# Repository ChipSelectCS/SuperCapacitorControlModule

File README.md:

# SuperCapacitorControlModule
250W backup supercapacitor module that fully overtakes main supply line(22-26V) in case of exceeding a programed threshold power with ability for recharge

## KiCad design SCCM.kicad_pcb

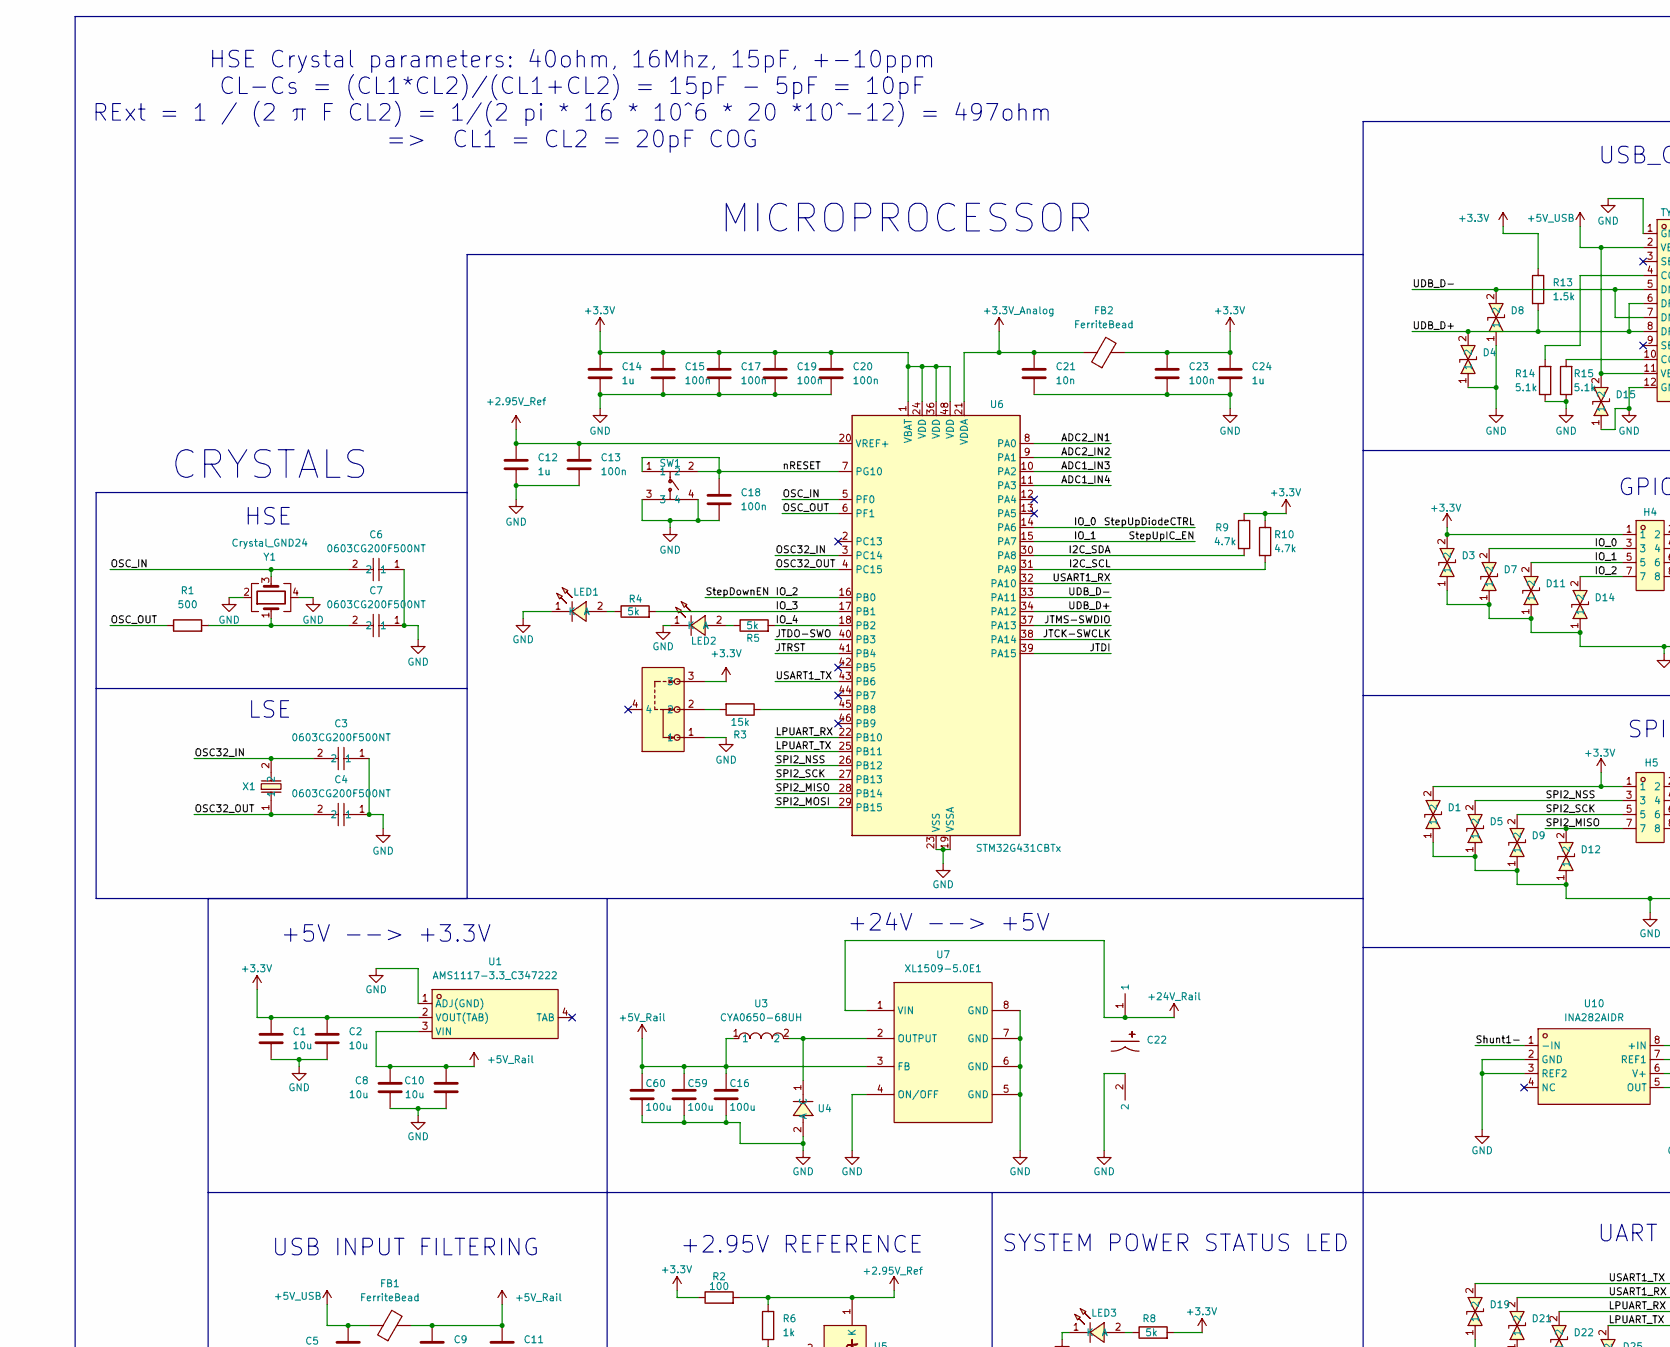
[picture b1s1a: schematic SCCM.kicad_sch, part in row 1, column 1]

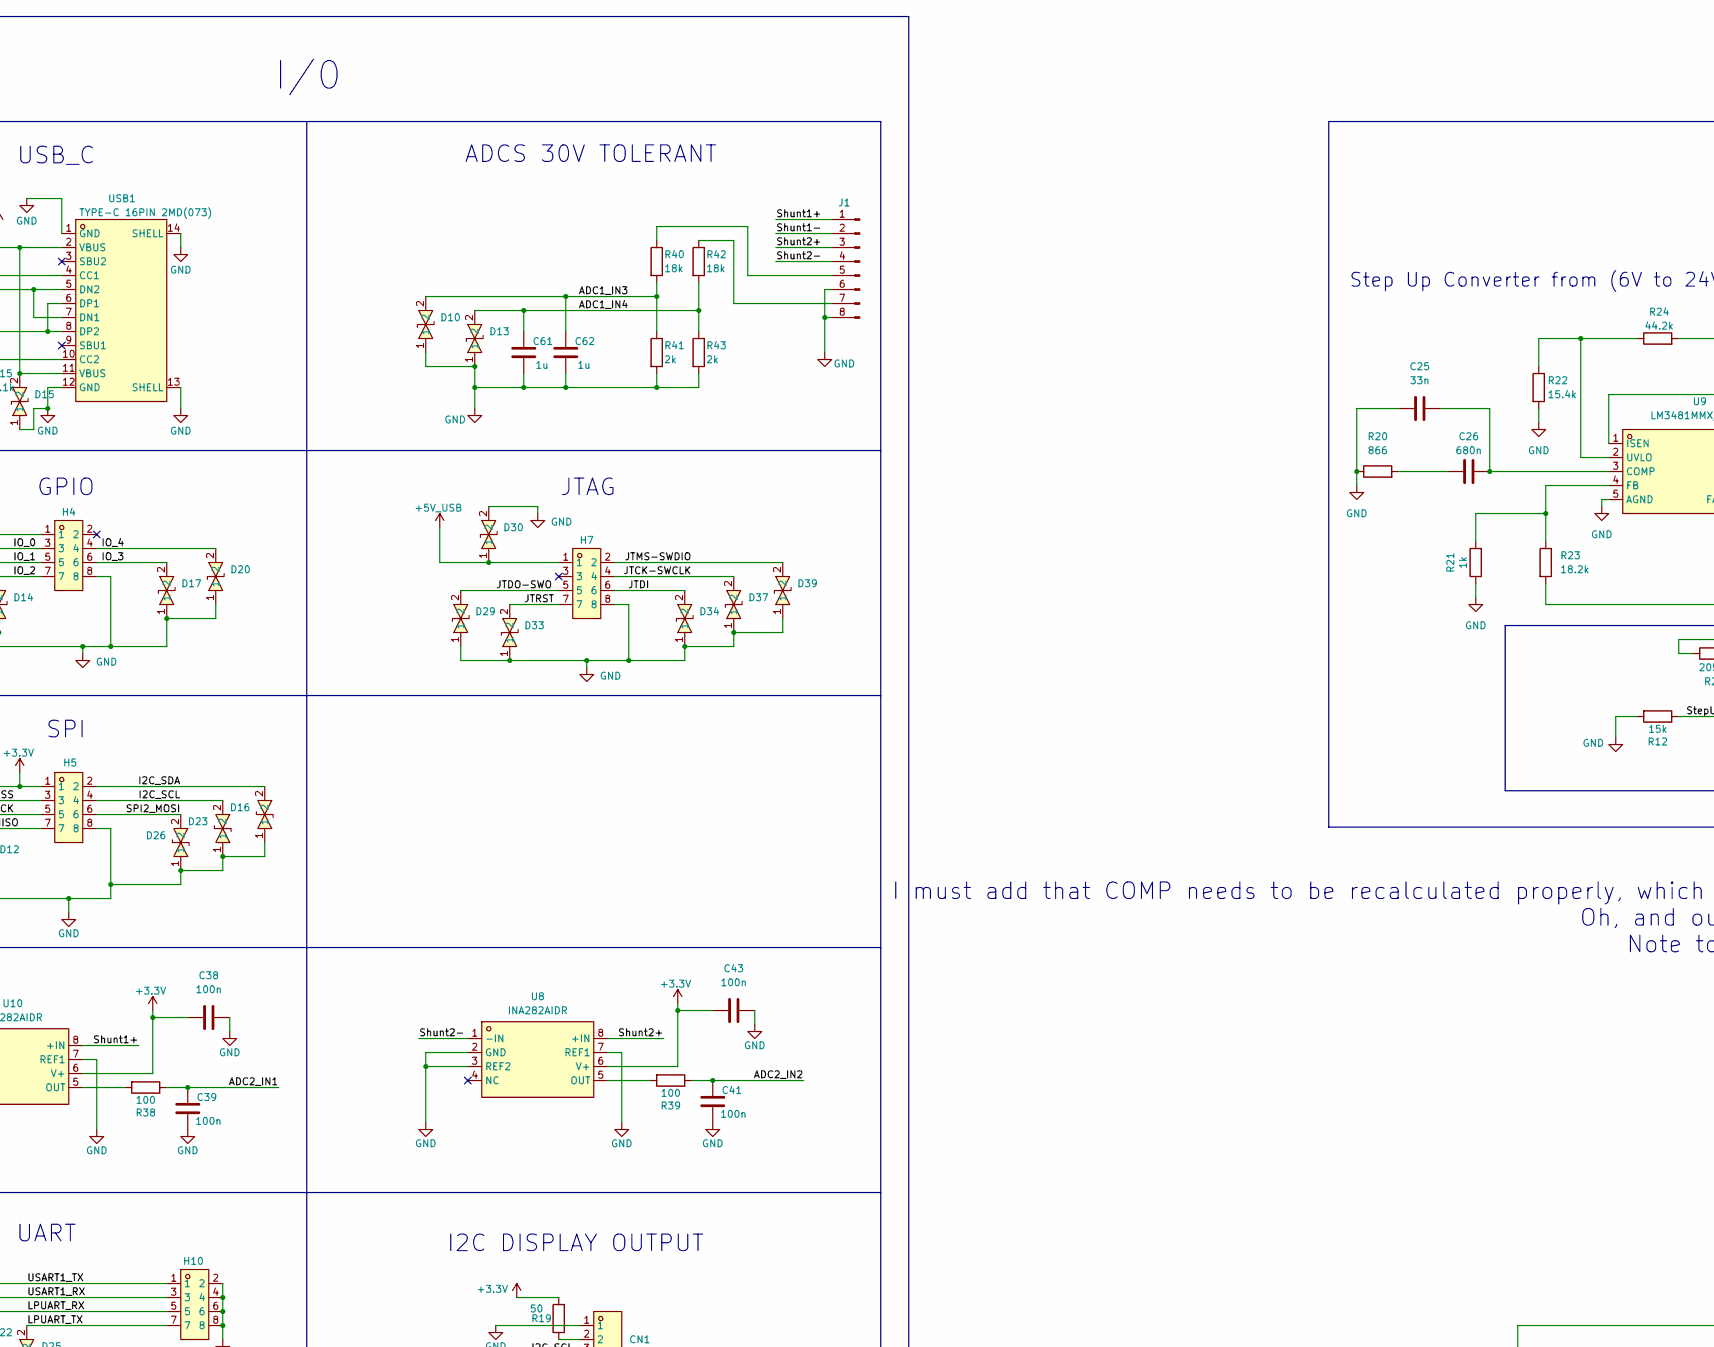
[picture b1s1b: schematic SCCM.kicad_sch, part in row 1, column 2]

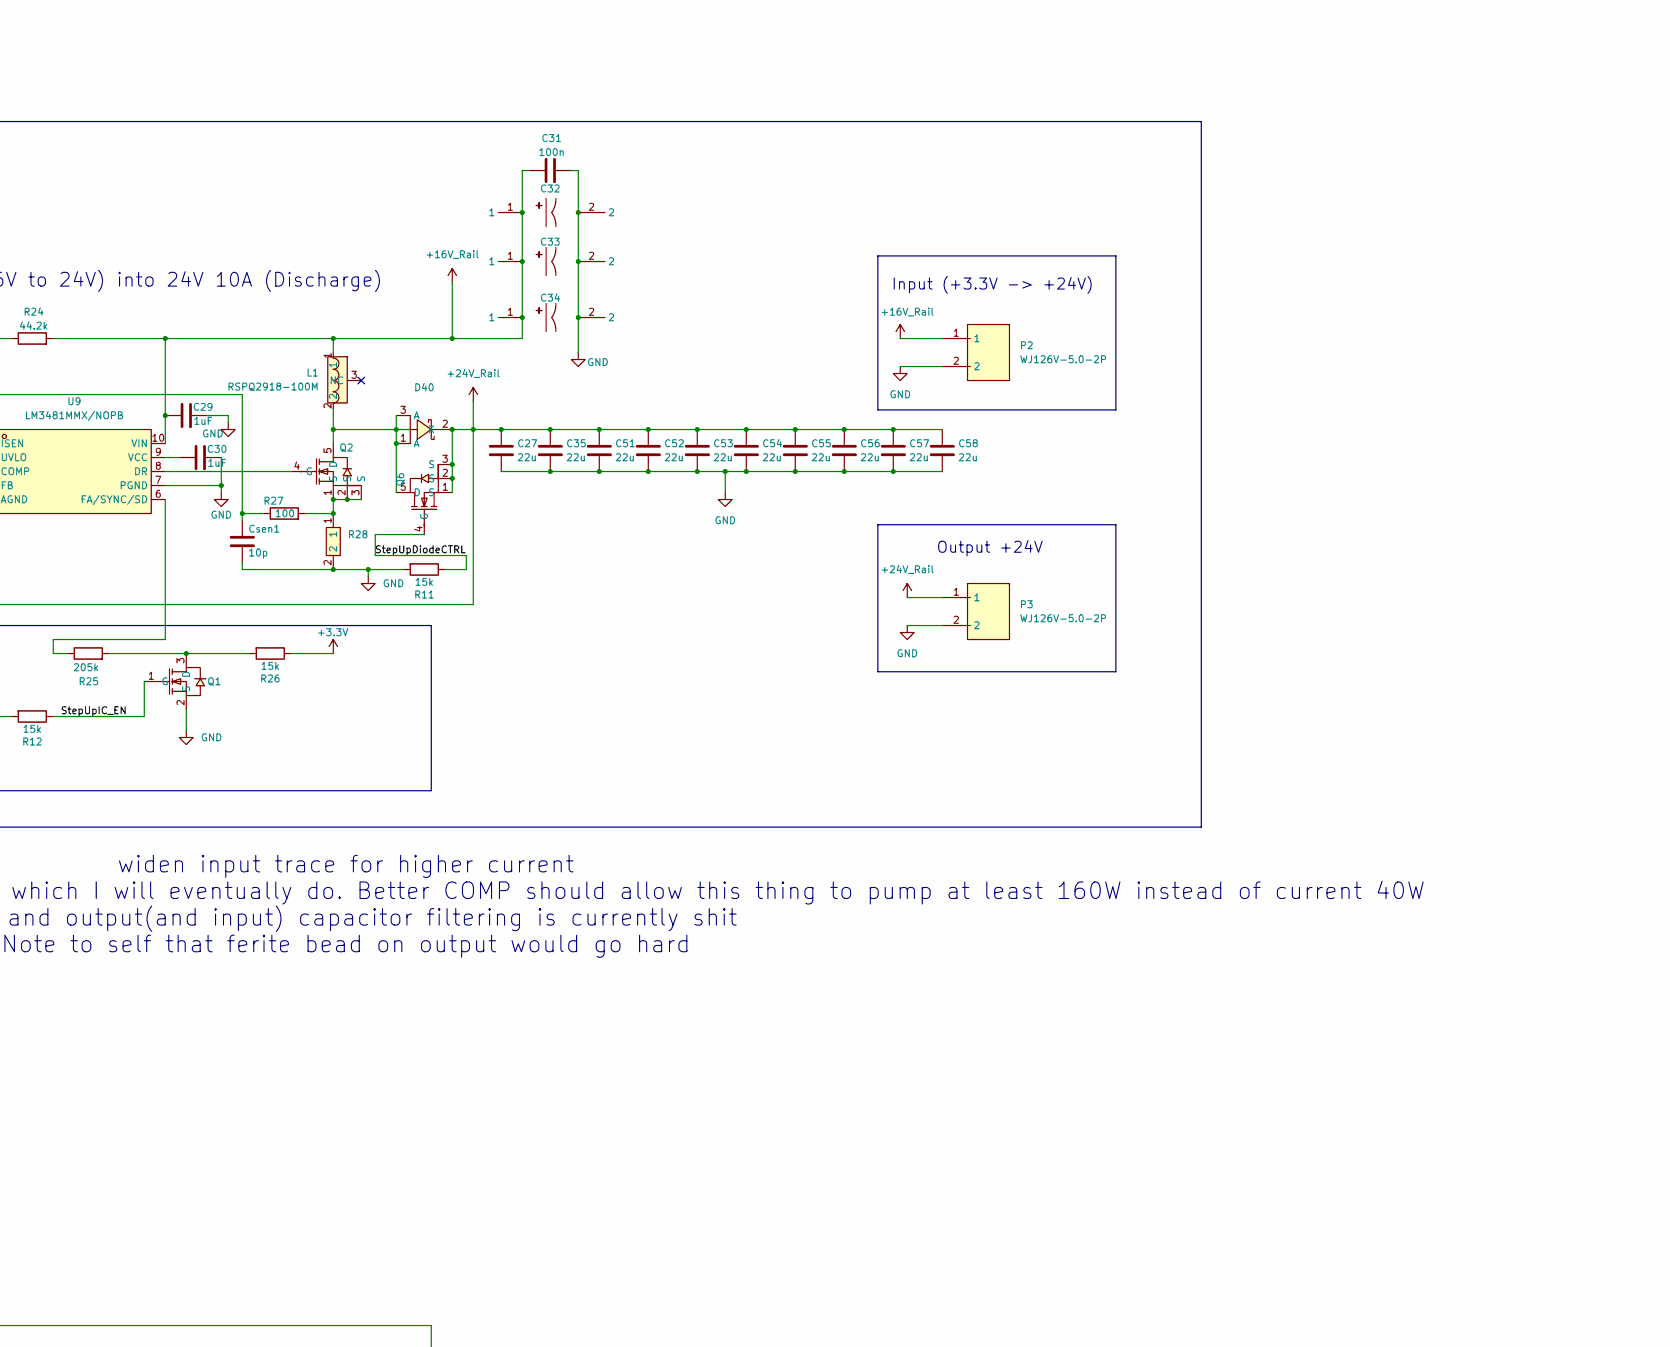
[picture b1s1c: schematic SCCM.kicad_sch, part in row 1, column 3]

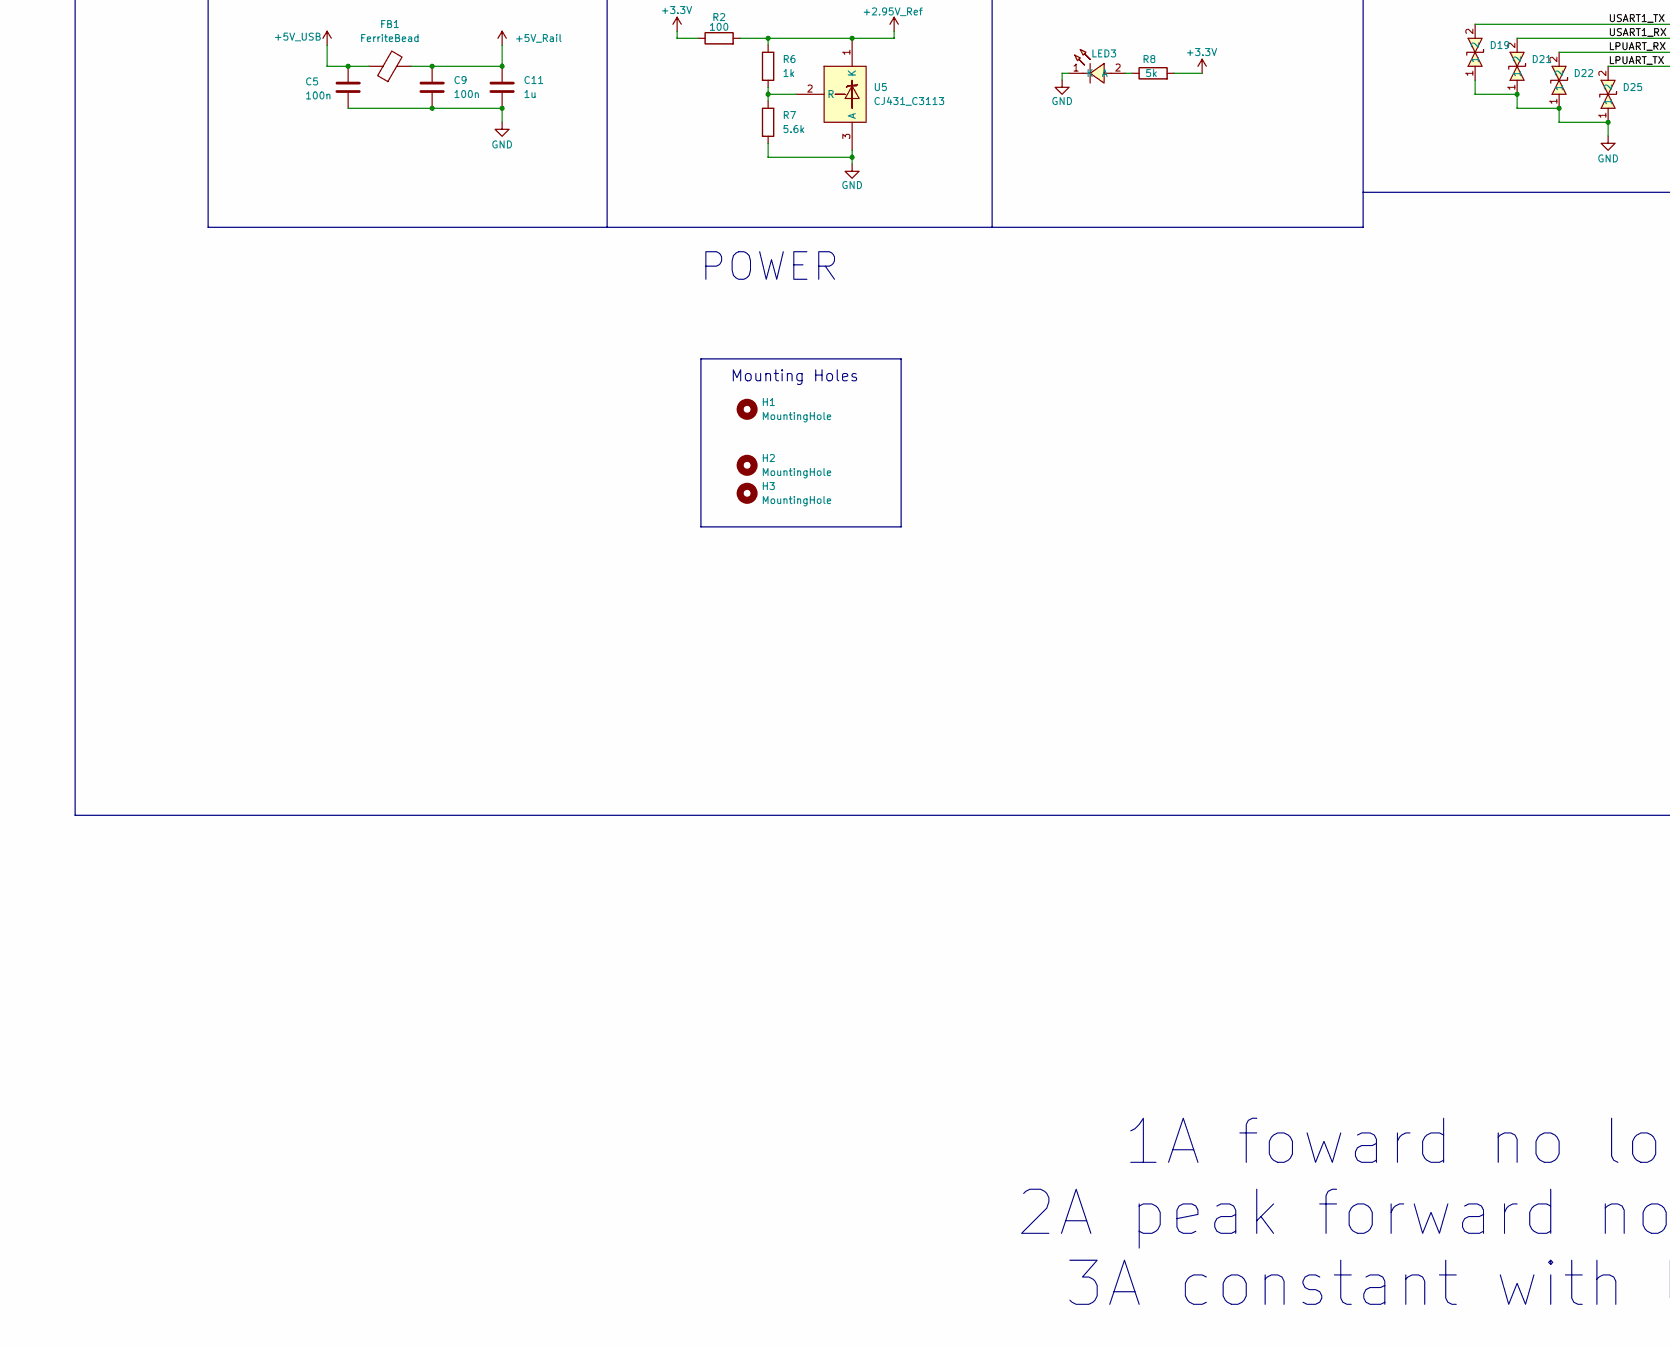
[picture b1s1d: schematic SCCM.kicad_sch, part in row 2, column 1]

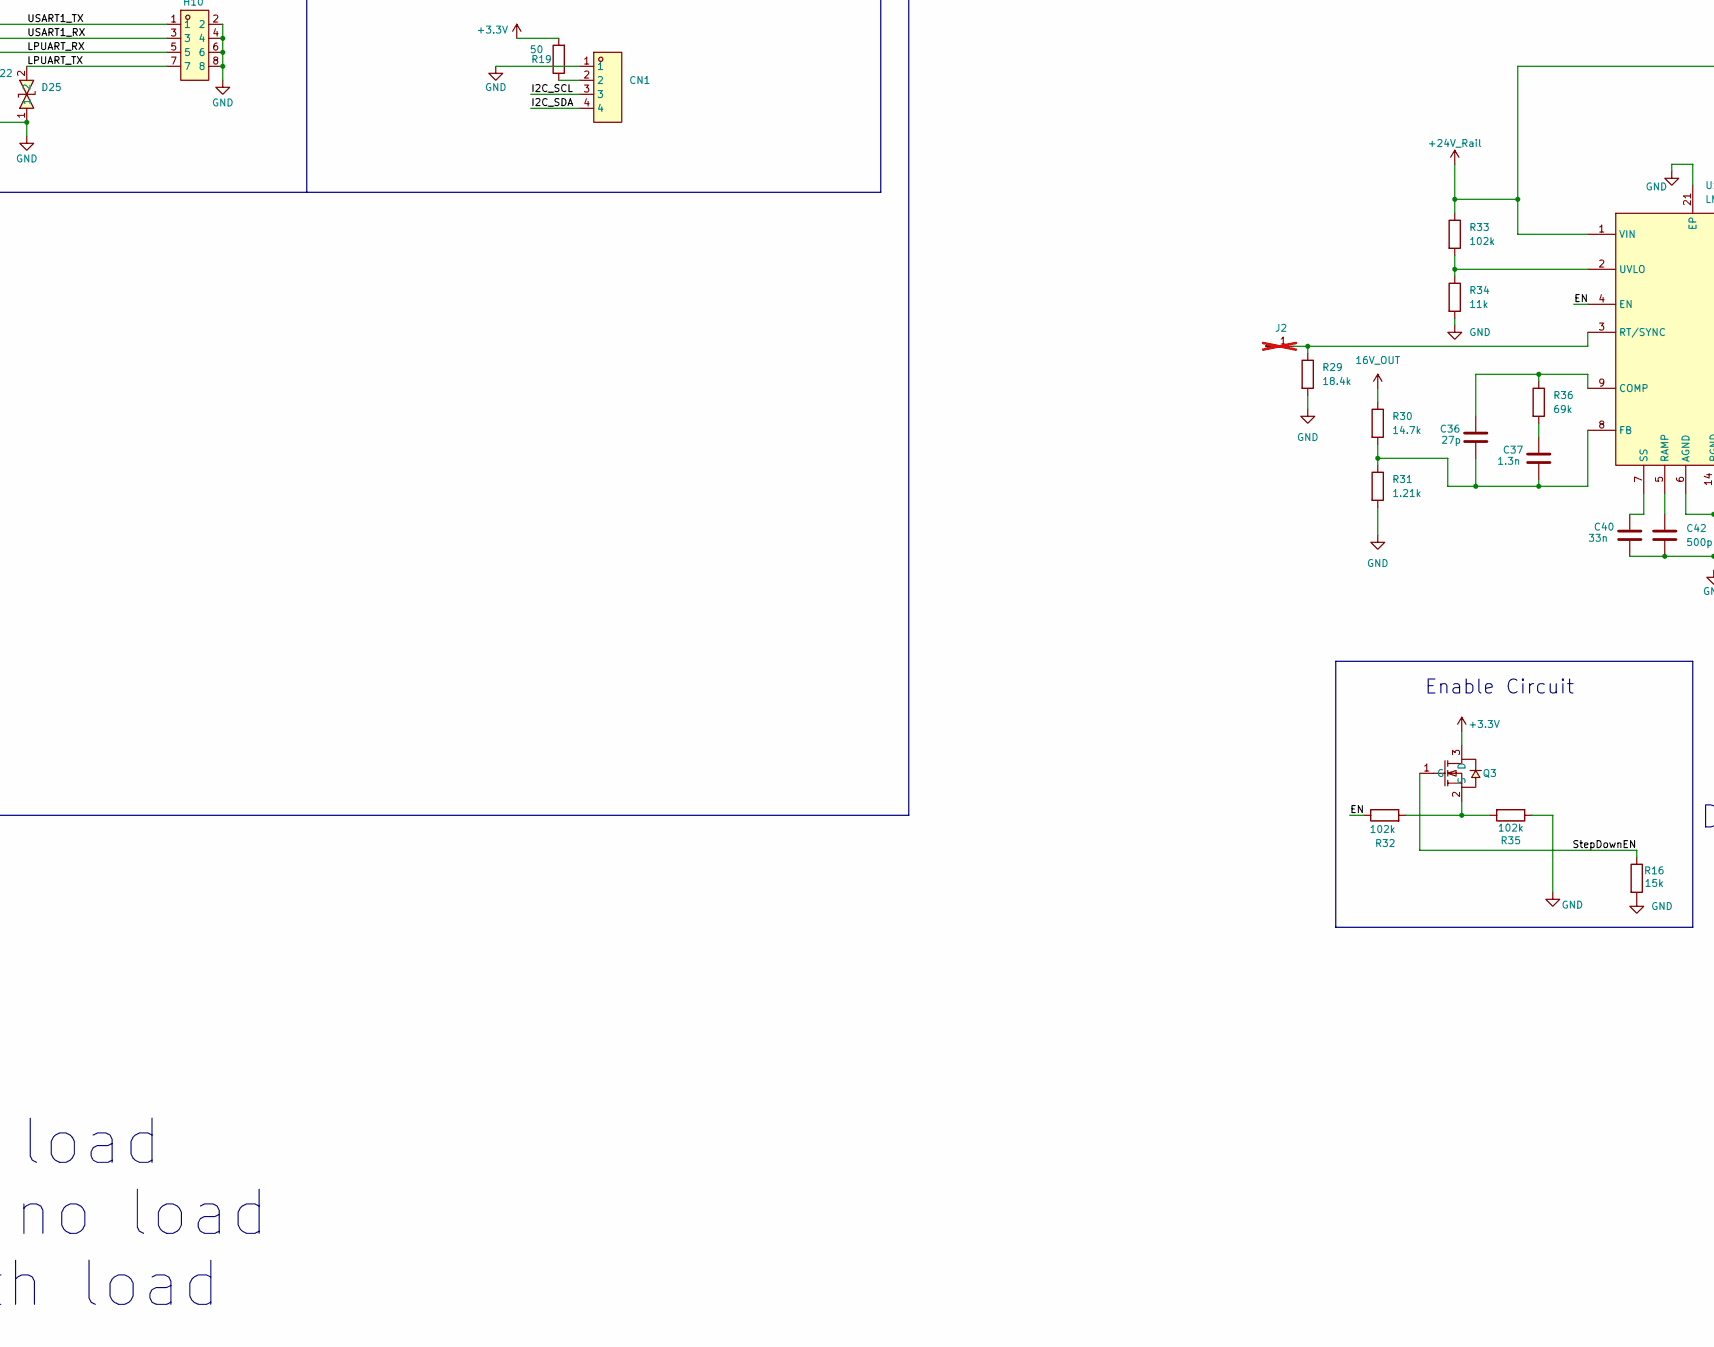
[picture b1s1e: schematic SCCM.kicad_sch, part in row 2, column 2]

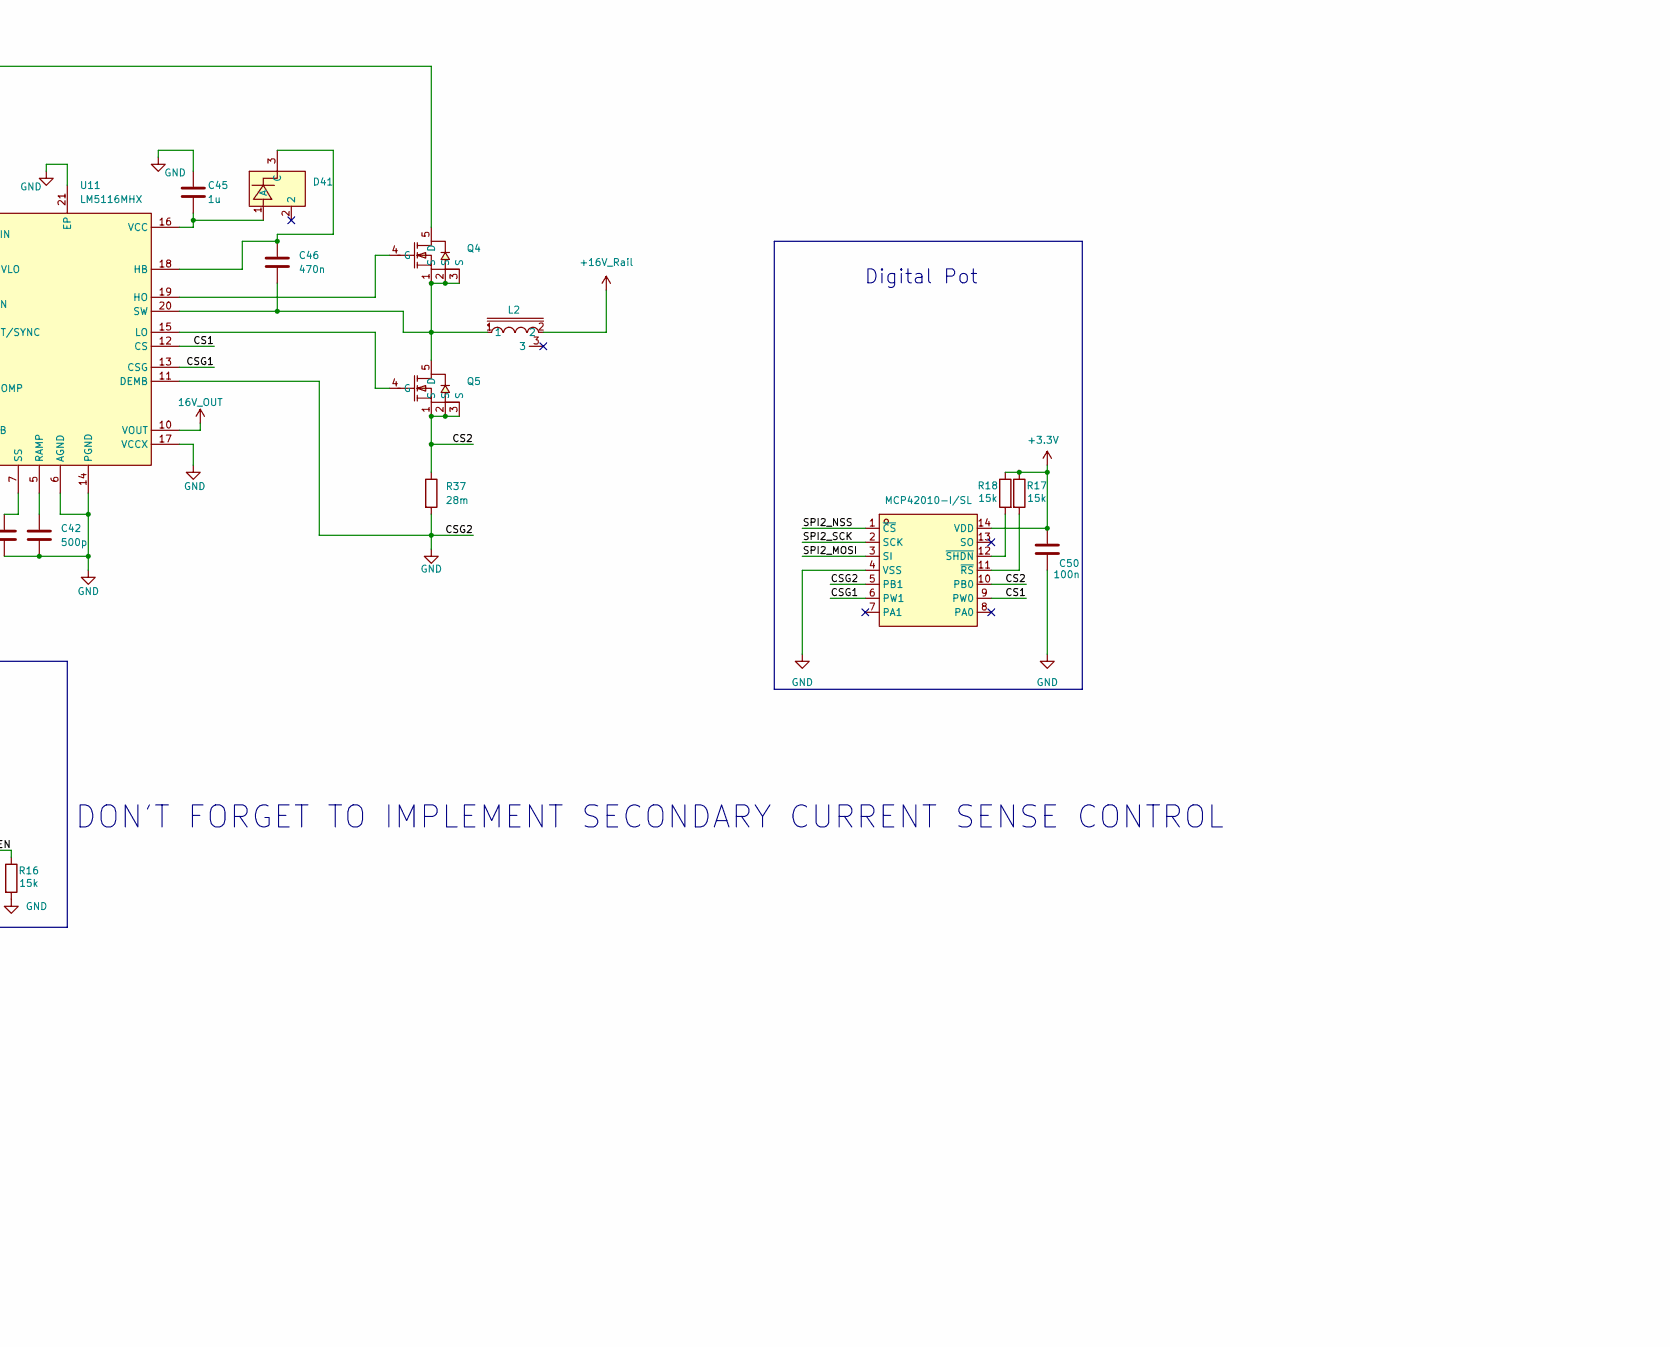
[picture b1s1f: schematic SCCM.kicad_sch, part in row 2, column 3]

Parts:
C1, C2, C8, C10: 10u; C_0603_1608Metric
C3, C4, C6, C7: 0603CG200F500NT; C0603; LCSC Part C165732
C5, C9, C13, C15, C17, C18, C19, C20, C23, C31, C38, C39, C41, C43, C50: 100n; C_0603_1608Metric
C11, C12, C14, C24, C45, C61, C62: 1u; C_0603_1608Metric
C16, C59, C60: 100u; C_1206_3216Metric; LCSC Part C7432784
C21: 10n; C_0603_1608Metric
C22, C32, C33, C34: HV1H227M1010PZ; CAP-SMD_BD10.0-L10.3-W10.3-LS11.3-FD; LCSC Part C5246564
C25, C40: 33n; C_0603_1608Metric
C26: 680n; C_0603_1608Metric
C27, C35, C51, C52, C53, C54, C55, C56, C57, C58: 22u; C_0805_2012Metric; LCSC Part C6119901
C29, C30: 1uF; C_0603_1608Metric
C36: 27p; C_0603_1608Metric
C37: 1.3n; C_0603_1608Metric
C42: 500p; C_0603_1608Metric
C46: 470n; C_0603_1608Metric
CN1: F136-1104S3CMUB2; HDR-SMD_4P-P2.54-V-M-LS5.0; LCSC Part C20071191
Csen1: 10p; C_0603_1608Metric
D1, D3, D4, D5, D7, D8, D9, D10, D11, D12, D13, D14, D15, D16, D17, D19, D20, D21, D22, D23, D25, D26, D29, D30, D33, D34, D37, D39: RCLAMP0521P-N; X1-DFN1006-2_L1.0-W0.6-P0.65-BI; LCSC Part C316043
D40: ST2045; TO-277_3P-L5.4-W4.0-LS6.5-BR; LCSC Part C840773
D41: BAS20LT1G; SOT-23-3_L2.9-W1.3-P1.90-LS2.4-BL-1; LCSC Part C232529
FB1, FB2: FerriteBead; L_0603_1608Metric
H1, H2, H3: MountingHole; MountingHole_2.2mm_M2
H4, H5, H7, H10: 2.54-2*4P立贴针; HDR-SMD_8P-P2.54-V-M-R2-C4-LS7.4; LCSC Part C192300
J1: Conn_01x08_Pin; PinHeader_1x08_P2.54mm_Vertical
J2: Conn_01x01_Pin; PinHeader_1x01_P2.54mm_Vertical; not fitted
L1: RSPQ2918-100M; IND-SMD_3P-L27.9-W19.7-P10.43-LS27.9-BL-A; LCSC Part C32712982
L2: FC-SE2918-220M; IND-SMD_3P-L27.9-W19.7-P10.43-LS27.9-BL-A; LCSC Part C2962789
LED1, LED2, LED3: XL-1608UGC-04; LED0603-RD_GREEN; LCSC Part C965804
P2, P3: WJ126V-5.0-2P; CONN-TH_WJ126V-5.0-2P; LCSC Part C8404
Q1, Q3: 2N7002K_C414015; SOT-23-3_L2.9-W1.3-P1.90-LS2.4-BR; LCSC Part C414015
Q2, Q4, Q5, Q6: BSC0702LS-HXY; TDSON-8_L5.9-W5.2-P1.27-BL; LCSC Part C20606289
R1: 500; R_0603_1608Metric
R2, R27, R38, R39: 100; R_0603_1608Metric
R3, R11, R12, R16, R17, R18, R26: 15k; R_0603_1608Metric
R4, R5, R8: 5k; R_0603_1608Metric
R6, R21: 1k; R_0603_1608Metric
R7: 5.6k; R_0603_1608Metric
R9, R10: 4.7k; R_0603_1608Metric
R13: 1.5k; R_0603_1608Metric
R14, R15: 5.1k; R_0603_1608Metric
R19: 50; R_0603_1608Metric
R20: 866; R_0603_1608Metric
R22: 15.4k; R_0603_1608Metric
R23: 18.2k; R_0603_1608Metric
R24: 44.2k; R_0603_1608Metric
R25: 205k; R_0603_1608Metric
R28: FRM252WFR0025TN; R2512; LCSC Part C7420002
R29: 18.4k; R_0603_1608Metric
R30: 14.7k; R_0603_1608Metric
R31: 1.21k; R_0603_1608Metric
R32, R33, R35: 102k; R_0603_1608Metric
R34: 11k; R_0603_1608Metric
R36: 69k; R_0603_1608Metric
R37: 28m; R_2512_6332Metric
R40, R42: 18k; R_0603_1608Metric
R41, R43: 2k; R_0603_1608Metric
SW1: GT-TZ084B-H015-L1; SW-SMD_4P-L5.2-W5.2-P3.70-LS6.4; LCSC Part C29780122
U1: AMS1117-3.3_C347222; SOT-223-4_L6.5-W3.5-P2.30-LS7.0-BR; LCSC Part C347222
U2: MSS12C02LS-BB2.0; SW-SMD_MSS12C02LS-HB2.0-1; LCSC Part C3008585
U3: CYA0650-68UH; IND-SMD_L7.2-W6.6_GPSR07X0; LCSC Part C5189964
U4: MBRA340T3G_C5563736; SMA_L4.5-W2.6-LS5.2-RD; LCSC Part C5563736
U5: CJ431_C3113; SOT-23-3_L2.9-W1.6-P1.90-LS2.8-BR; LCSC Part C3113
U6: STM32G431CBTx; LQFP-48_7x7mm_P0.5mm
U7: XL1509-5.0E1; SOIC-8_L5.0-W4.0-P1.27-LS6.0-BL; LCSC Part C61063
U8, U10: INA282AIDR; SOIC-8_L4.9-W3.9-P1.27-LS6.0-BL; LCSC Part C53319
U9: LM3481MMX/NOPB; VSSOP-10_L3.0-W3.0-P0.50-LS4.9-BL; LCSC Part C543002
U11: LM5116MHX; HTSSOP-20_L6.5-W4.4-P0.65-LS6.4-BL-EP; LCSC Part C13755
U14: MCP42010-I/SL; SOIC-14_L8.7-W3.9-P1.27-LS6.0-BL; LCSC Part C481366
USB1: TYPE-C 16PIN 2MD(073); USB-C-SMD_TYPE-C-6PIN-2MD-073; LCSC Part C2765186
X1: Q13FC1350000400; FC-135R_L3.2-W1.5; LCSC Part C32346
Y1: Crystal_GND24; Crystal_SMD_3225-4Pin_3.2x2.5mm

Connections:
16V_OUT: R30.1, U11.10 (VOUT)
+2.95V_Ref: C12.1, C13.1, R2.2, R6.1, U5.1 (K), U6.20 (VREF+)
+3.3V: C1.1, C2.1, C14.1, C15.1, C17.1, C19.1, C20.1, C23.1, C24.1, C38.1, C43.1, C50.1, D1.2, D3.2, FB2.2, H4.1, H5.1, Q3.3 (D), R2.1, R8.2, R9.1, R10.1, R13.1, R17.1, R18.1, R19.2, R26.1, U1.2 (VOUT(TAB)), U2.3, U6.1 (VBAT), U6.24 (VDD), U6.36 (VDD), U6.48 (VDD), U8.6 (V+), U10.6 (V+), U14.14 (VDD)
+3.3V_Analog: C21.1, FB2.1, U6.21 (VDDA)
+5V_Rail: C8.1, C9.1, C10.1, C11.1, C16.1, C59.1, C60.1, FB1.2, U1.3 (VIN), U3.1, U7.3 (FB)
+5V_USB: C5.1, D15.2, D30.1, FB1.1, H7.1, USB1.2 (VBUS), USB1.11 (VBUS)
+16V_Rail: C29.1, C31.2, C32.1, C33.1, C34.1, L1.1, L2.2, P2.1, R24.2, U9.10 (VIN)
+24V_Rail: C22.1, C27.1, C35.1, C51.1, C52.1, C53.1, C54.1, C55.1, C56.1, C57.1, C58.1, D40.2 (K), P3.1, Q4.5 (D), Q6.1 (S), Q6.2 (S), Q6.3 (S), R23.2, R33.1, U7.1 (VIN), U11.1 (VIN)
/ADC1_IN3: C62.1, D10.2, R40.2, R41.1, U6.10 (PA2)
/ADC1_IN4: C61.1, D13.2, R42.2, R43.1, U6.11 (PA3)
/ADC2_IN1: C39.2, R38.1, U6.8 (PA0)
/ADC2_IN2: C41.2, R39.1, U6.9 (PA1)
/CS1: U11.12 (CS), U14.9 (PW0)
/CS2: Q5.1 (S), Q5.2 (S), Q5.3 (S), R37.1, U14.10 (PB0)
/CSG1: U11.13 (CSG), U14.6 (PW1)
/EN: R32.1, U11.4 (EN)
/I2C_SCL: CN1.3, D23.2, H5.4, R10.2, U6.31 (PA9)
/I2C_SDA: CN1.4, D16.2, H5.2, R9.2, U6.30 (PA8)
/IO_0: D7.2, H4.3, Q6.4 (G), R11.1, U6.14 (PA6)
/IO_1: D11.2, H4.5, Q1.1 (G), R12.1, U6.15 (PA7)
/IO_2: D14.2, H4.7, Q3.1 (G), R16.1, U6.16 (PB0)
/IO_3: D17.2, H4.6, R4.2, U6.17 (PB1)
/IO_4: D20.2, H4.4, R5.2, U6.18 (PB2)
/JTCK-SWCLK: D37.2, H7.4, U6.38 (PA14)
/JTDI: D34.2, H7.6, U6.39 (PA15)
/JTDO-SWO: D29.2, H7.5, U6.40 (PB3)
/JTMS-SWDIO: D39.2, H7.2, U6.37 (PA13)
/JTRST: D33.2, H7.7, U6.41 (PB4)
/LPUART_RX: D22.2, H10.5, U6.22 (PB10)
/LPUART_TX: D25.2, H10.7, U6.25 (PB11)
/OSC32_IN: C3.2, U6.3 (PC14), X1.2
/OSC32_OUT: C4.2, U6.4 (PC15), X1.1
/OSC_IN: C6.2, U6.5 (PF0), Y1.3
/OSC_OUT: R1.1, U6.6 (PF1)
/SPI2_MISO: D12.2, H5.7, U6.28 (PB14)
/SPI2_MOSI: D26.2, H5.6, U6.29 (PB15), U14.3 (SI)
/SPI2_NSS: D5.2, H5.3, U6.26 (PB12), U14.1 (~CS)
/SPI2_SCK: D9.2, H5.5, U6.27 (PB13), U14.2 (SCK)
/Shunt1+: J1.1, U10.8 (+IN)
/Shunt1-: J1.2, U10.1 (-IN)
/Shunt2+: J1.3, U8.8 (+IN)
/Shunt2-: J1.4, U8.1 (-IN)
/UDB_D+: D4.2, R13.2, U6.34 (PA12), USB1.6 (DP1), USB1.8 (DP2)
/UDB_D-: D8.2, U6.33 (PA11), USB1.5 (DN2), USB1.7 (DN1)
/USART1_RX: D21.2, H10.3, U6.32 (PA10)
/USART1_TX: D19.2, H10.1, U6.43 (PB6)
/nRESET: C18.1, SW1.1, SW1.2, U6.7 (PG10)
GND: C1.2, C2.2, C3.1, C4.1, C5.2, C6.1, C7.1, C8.2, C9.2, C10.2, C11.2, C12.2, C13.2, C14.2, C15.2, C16.2, C17.2, C18.2, C19.2, C20.2, C21.2, C22.2, C23.2, C24.2, C25.1, C27.2, C29.2, C30.2, C31.1, C32.2, C33.2, C34.2, C35.2, C38.2, C39.1, C40.2, C41.1, C42.2, C43.2, C45.1, C50.2, C51.2, C52.2, C53.2, C54.2, C55.2, C56.2, C57.2, C58.2, C59.2, C60.2, C61.2, C62.2, CN1.1, Csen1.1, D1.1, D3.1, D4.1, D5.1, D7.1, D8.1, D9.1, D10.1, D11.1, D12.1, D13.1, D14.1, D15.1, D16.1, D17.1, D19.1, D20.1, D21.1, D22.1, D23.1, D25.1, D26.1, D29.1, D30.2, D33.1, D34.1, D37.1, D39.1, H4.8, H5.8, H7.8, H10.2, H10.4, H10.6, H10.8, J1.6, J1.8, LED1.1 (K), LED2.1 (K), LED3.1 (K), P2.2, P3.2, Q1.2 (S), R7.2, R11.2, R12.2, R14.1, R15.1, R16.2, R20.1, R21.1, R22.2, R28.2, R29.2, R31.2, R34.2, R35.1, R37.2, R41.2, R43.2, SW1.3, SW1.4, U1.1 (ADJ(GND)), U2.1, U4.2 (A), U5.3 (A), U6.19 (VSSA), U6.23 (VSS), U6.35 (VSS), U6.47 (VSS), U7.4 (ON/OFF), U7.5 (GND), U7.6 (GND), U7.7 (GND), U7.8 (GND), U8.2 (GND), U8.3 (REF2), U8.7 (REF1), U9.5 (AGND), U9.7 (PGND), U10.2 (GND), U10.3 (REF2), U10.7 (REF1), U11.6 (AGND), U11.11 (DEMB), U11.14 (PGND), U11.17 (VCCX), U11.21 (EP), U14.4 (VSS), U14.5 (PB1), USB1.1 (GND), USB1.12 (GND), USB1.13 (SHELL), USB1.14 (SHELL), Y1.2, Y1.4
unnamed: C7.2, R1.2, Y1.1
unnamed: C26.1, R20.2
unnamed: C37.1, R36.2
unnamed: CN1.2, R19.1
unnamed: C45.2, D41.1 (A), U11.16 (VCC)
unnamed: C46.1, D41.3 (C), U11.18 (HB)
unnamed: J1.5, R40.1
unnamed: J1.7, R42.1
unnamed: J2.1, R29.1, U11.3 (RT/SYNC)
unnamed: LED1.2 (A), R4.1
unnamed: LED2.2 (A), R5.1
unnamed: LED3.2 (A), R8.1
unnamed: Q1.3 (D), R25.2, R26.2
unnamed: D40.1 (A), D40.3 (A), L1.2, Q2.5 (D), Q6.5 (D)
unnamed: Q2.4 (G), U9.8 (DR)
unnamed: Q2.1 (S), Q2.2 (S), Q2.3 (S), R27.2, R28.1
unnamed: Q3.2 (S), R32.2, R35.2
unnamed: Q4.4 (G), U11.19 (HO)
unnamed: C46.2, L2.1, Q4.1 (S), Q4.2 (S), Q4.3 (S), Q5.5 (D), U11.20 (SW)
unnamed: Q5.4 (G), U11.15 (LO)
unnamed: R3.2, U2.2
unnamed: U3.2, U4.1 (C), U7.2 (OUTPUT)
unnamed: R6.2, R7.1, U5.2 (R)
unnamed: R3.1, U6.45 (PB8)
unnamed: R39.2, U8.5 (OUT)
unnamed: C25.2, C26.2, U9.3 (COMP)
unnamed: R25.1, U9.6 (FA/SYNC/SD)
unnamed: R21.2, R23.1, U9.4 (FB)
unnamed: Csen1.2, R27.1, U9.1 (ISEN)
unnamed: R22.1, R24.1, U9.2 (UVLO)
unnamed: C30.1, U9.9 (VCC)
unnamed: R38.2, U10.5 (OUT)
unnamed: C36.1, R36.1, U11.9 (COMP)
unnamed: C36.2, C37.2, R30.2, R31.1, U11.8 (FB)
unnamed: C42.1, U11.5 (RAMP)
unnamed: C40.1, U11.7 (SS)
unnamed: R33.2, R34.1, U11.2 (UVLO)
unnamed: R17.2, U14.11 (~RS)
unnamed: R18.2, U14.12 (~SHDN)
unnamed: R14.2, USB1.4 (CC1)
unnamed: R15.2, USB1.10 (CC2)

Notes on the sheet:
+2.95V REFERENCE
CRYSTALS
Digital Pot
Output +24V
I/0
DON'T FORGET TO IMPLEMENT SECONDARY CURRENT SENSE CONTROL
Enable Circuit
Step Up Converter from (6V to 24V) into 24V 10A (Discharge)
ADCS 30V TOLERANT
GPIO
+24V --> +5V
SPI
Mounting Holes
UART
LSE
HSE
HSE Crystal parameters: 40ohm, 16Mhz, 15pF, +-10ppm CL-Cs = (CL1*CL2)/(CL1+CL2) = 15pF - 5pF = 10pF RExt = 1 / (2 π F CL2) = 1/(2 pi * 16 * 10^6 * 20 *10^-12) = 497ohm => CL1 = CL2 = 20pF COG
+5V --> +3.3V
POWER
widen input trace for higher current I must add that COMP needs to be recalculated properly, which I will eventually do. Better COMP should allow this thing to pump at least 160W instead of current 40W Oh, and output(and input) capacitor filtering is currently shit Note to self that ferite bead on 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
USB INPUT FILTERING
JTAG
1A foward no load 2A peak forward no load 3A constant with load
MICROPROCESSOR
Input (+3.3V -> +24V)
I2C DISPLAY OUTPUT
SYSTEM POWER STATUS LED
USB_C

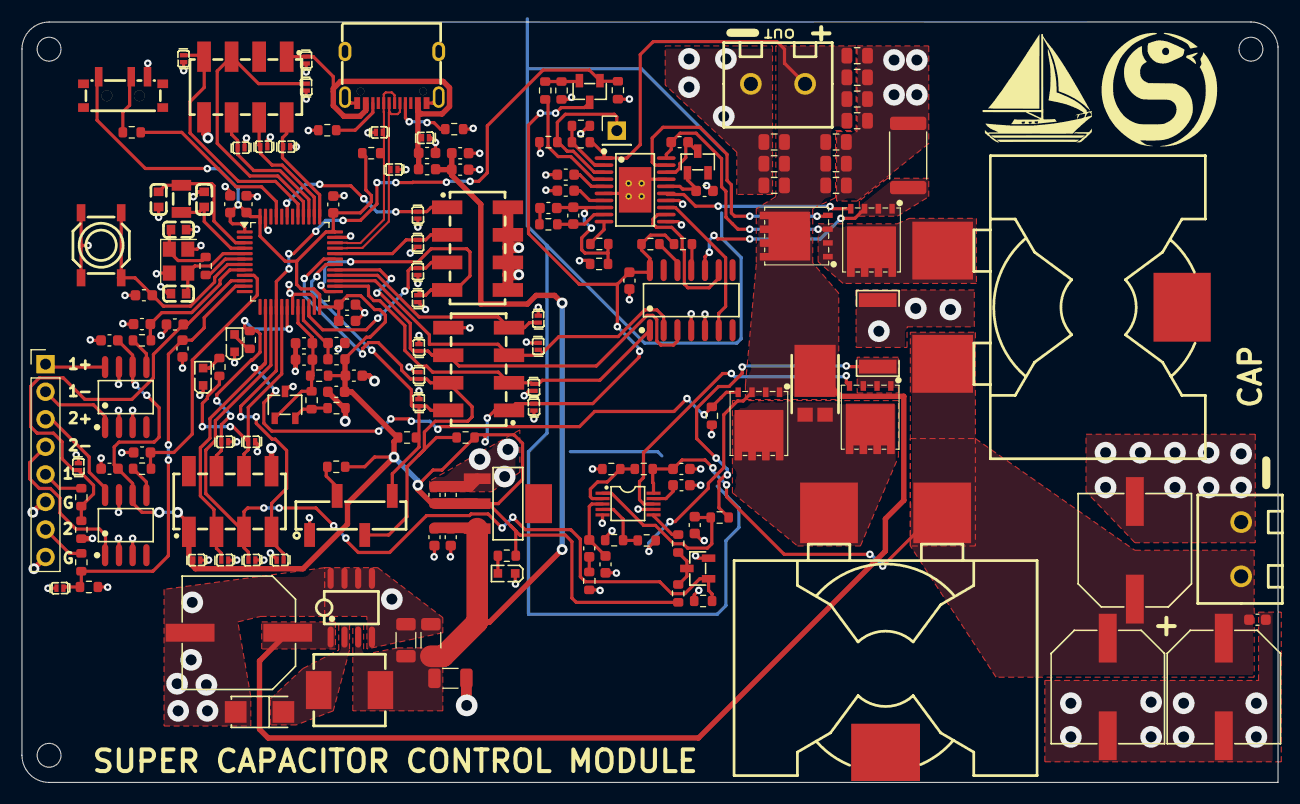
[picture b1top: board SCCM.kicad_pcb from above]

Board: 2 copper layers, 115.8 x 70.1 mm, 172 parts (0 on the bottom side), 89 nets.

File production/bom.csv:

Designator,Footprint,Quantity,Value,LCSC Part #
"C1, C10, C2, C8",0603,4,10u,
"C11, C12, C14, C24, C45, C61, C62",0603,7,1u,
"C13, C15, C17, C18, C19, C20, C23, C31, C38, C39, C41, C43, C5, C50, C9",0603,15,100n,
"C16, C59, C60",1206,3,100u,C7432784
C21,0603,1,10n,
"C22, C32, C33, C34",CAP-SMD_BD10.0-L10.3-W10.3-LS11.3-FD,4,HV1H227M1010PZ,C5246564
"C25, C40",0603,2,33n,
C26,0603,1,680n,
"C27, C35, C51, C52, C53, C54, C55, C56, C57, C58",0805,10,22u,C6119901
"C29, C30",0603,2,1uF,
"C3, C4, C6, C7",C0603,4,0603CG200F500NT,C165732
C36,0603,1,27p,
C37,0603,1,1.3n,
C42,0603,1,500p,
C46,0603,1,470n,
CN1,HDR-SMD_4P-P2.54-V-M-LS5.0,1,F136-1104S3CMUB2,C20071191
CSEN1,0603,1,10p,
"D1, D10, D11, D12, D13, D14, D15, D16, D17, D19, D20, D21, D22, D23, D25, D26, D29, D3, D30, D33, D34, D37, D39, D4, D5, D7, D8, D9",X1-DFN1006-2_L1.0-W0.6-P0.65-BI,28,RCLAMP0521P-N,C316043
D40,TO-277_3P-L5.4-W4.0-LS6.5-BR,1,ST2045,C840773
D41,SOT-23-3_L2.9-W1.3-P1.90-LS2.4-BL-1,1,BAS20LT1G,C232529
"FB1, FB2",0603,2,FerriteBead,
"H10, H4, H5, H7",HDR-SMD_8P-P2.54-V-M-R2-C4-LS7.4,4,2.54-2*4P立贴针,C192300
J1,PinHeader_1x08_P2.54mm_Vertical,1,Conn_01x08_Pin,
J2,PinHeader_1x01_P2.54mm_Vertical,1,Conn_01x01_Pin,
L1,IND-SMD_3P-L27.9-W19.7-P10.43-LS27.9-BL-A,1,RSPQ2918-100M,C32712982
L2,IND-SMD_3P-L27.9-W19.7-P10.43-LS27.9-BL-A,1,FC-SE2918-220M,C2962789
"LED1, LED2, LED3",LED0603-RD_GREEN,3,XL-1608UGC-04,C965804
"P2, P3",CONN-TH_WJ126V-5.0-2P,2,WJ126V-5.0-2P,C8404
"Q1, Q3",SOT-23-3_L2.9-W1.3-P1.90-LS2.4-BR,2,2N7002K_C414015,C414015
"Q2, Q4, Q5, Q6",TDSON-8_L5.9-W5.2-P1.27-BL,4,BSC0702LS-HXY,C20606289
R1,0603,1,500,
"R10, R9",0603,2,4.7k,
"R11, R12, R16, R17, R18, R26, R3",0603,7,15k,
R13,0603,1,1.5k,
"R14, R15",0603,2,5.1k,
R19,0603,1,50,
"R2, R27, R38, R39",0603,4,100,
R20,0603,1,866,
"R21, R6",0603,2,1k,
R22,0603,1,15.4k,
R23,0603,1,18.2k,
R24,0603,1,44.2k,
R25,0603,1,205k,
R28,R2512,1,FRM252WFR0025TN,C7420002
R29,0603,1,18.4k,
R30,0603,1,14.7k,
R31,0603,1,1.21k,
"R32, R33, R35",0603,3,102k,
R34,0603,1,11k,
R36,0603,1,69k,
R37,2512,1,28m,
"R4, R5, R8",0603,3,5k,
"R40, R42",0603,2,18k,
"R41, R43",0603,2,2k,
R7,0603,1,5.6k,
SW1,SW-SMD_4P-L5.2-W5.2-P3.70-LS6.4,1,GT-TZ084B-H015-L1,C29780122
U1,SOT-223-4_L6.5-W3.5-P2.30-LS7.0-BR,1,AMS1117-3.3_C347222,C347222
"U10, U8",SOIC-8_L4.9-W3.9-P1.27-LS6.0-BL,2,INA282AIDR,C53319
U11,HTSSOP-20_L6.5-W4.4-P0.65-LS6.4-BL-EP,1,LM5116MHX,C13755
U14,SOIC-14_L8.7-W3.9-P1.27-LS6.0-BL,1,MCP42010-I/SL,C481366
U2,SW-SMD_MSS12C02LS-HB2.0-1,1,MSS12C02LS-BB2.0,C3008585
U3,IND-SMD_L7.2-W6.6_GPSR07X0,1,CYA0650-68UH,C5189964
U4,SMA_L4.5-W2.6-LS5.2-RD,1,MBRA340T3G_C5563736,C5563736
U5,SOT-23-3_L2.9-W1.6-P1.90-LS2.8-BR,1,CJ431_C3113,C3113
U6,LQFP-48_7x7mm_P0.5mm,1,STM32G431CBTx,
U7,SOIC-8_L5.0-W4.0-P1.27-LS6.0-BL,1,XL1509-5.0E1,C61063
U9,VSSOP-10_L3.0-W3.0-P0.50-LS4.9-BL,1,LM3481MMX/NOPB,C543002
USB1,USB-C-SMD_TYPE-C-6PIN-2MD-073,1,TYPE-C 16PIN 2MD(073),C2765186
X1,FC-135R_L3.2-W1.5,1,Q13FC1350000400,C32346
Y1,Crystal_SMD_3225-4Pin_3.2x2.5mm,1,Crystal_GND24,

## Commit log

2026-04-14 File Upload
